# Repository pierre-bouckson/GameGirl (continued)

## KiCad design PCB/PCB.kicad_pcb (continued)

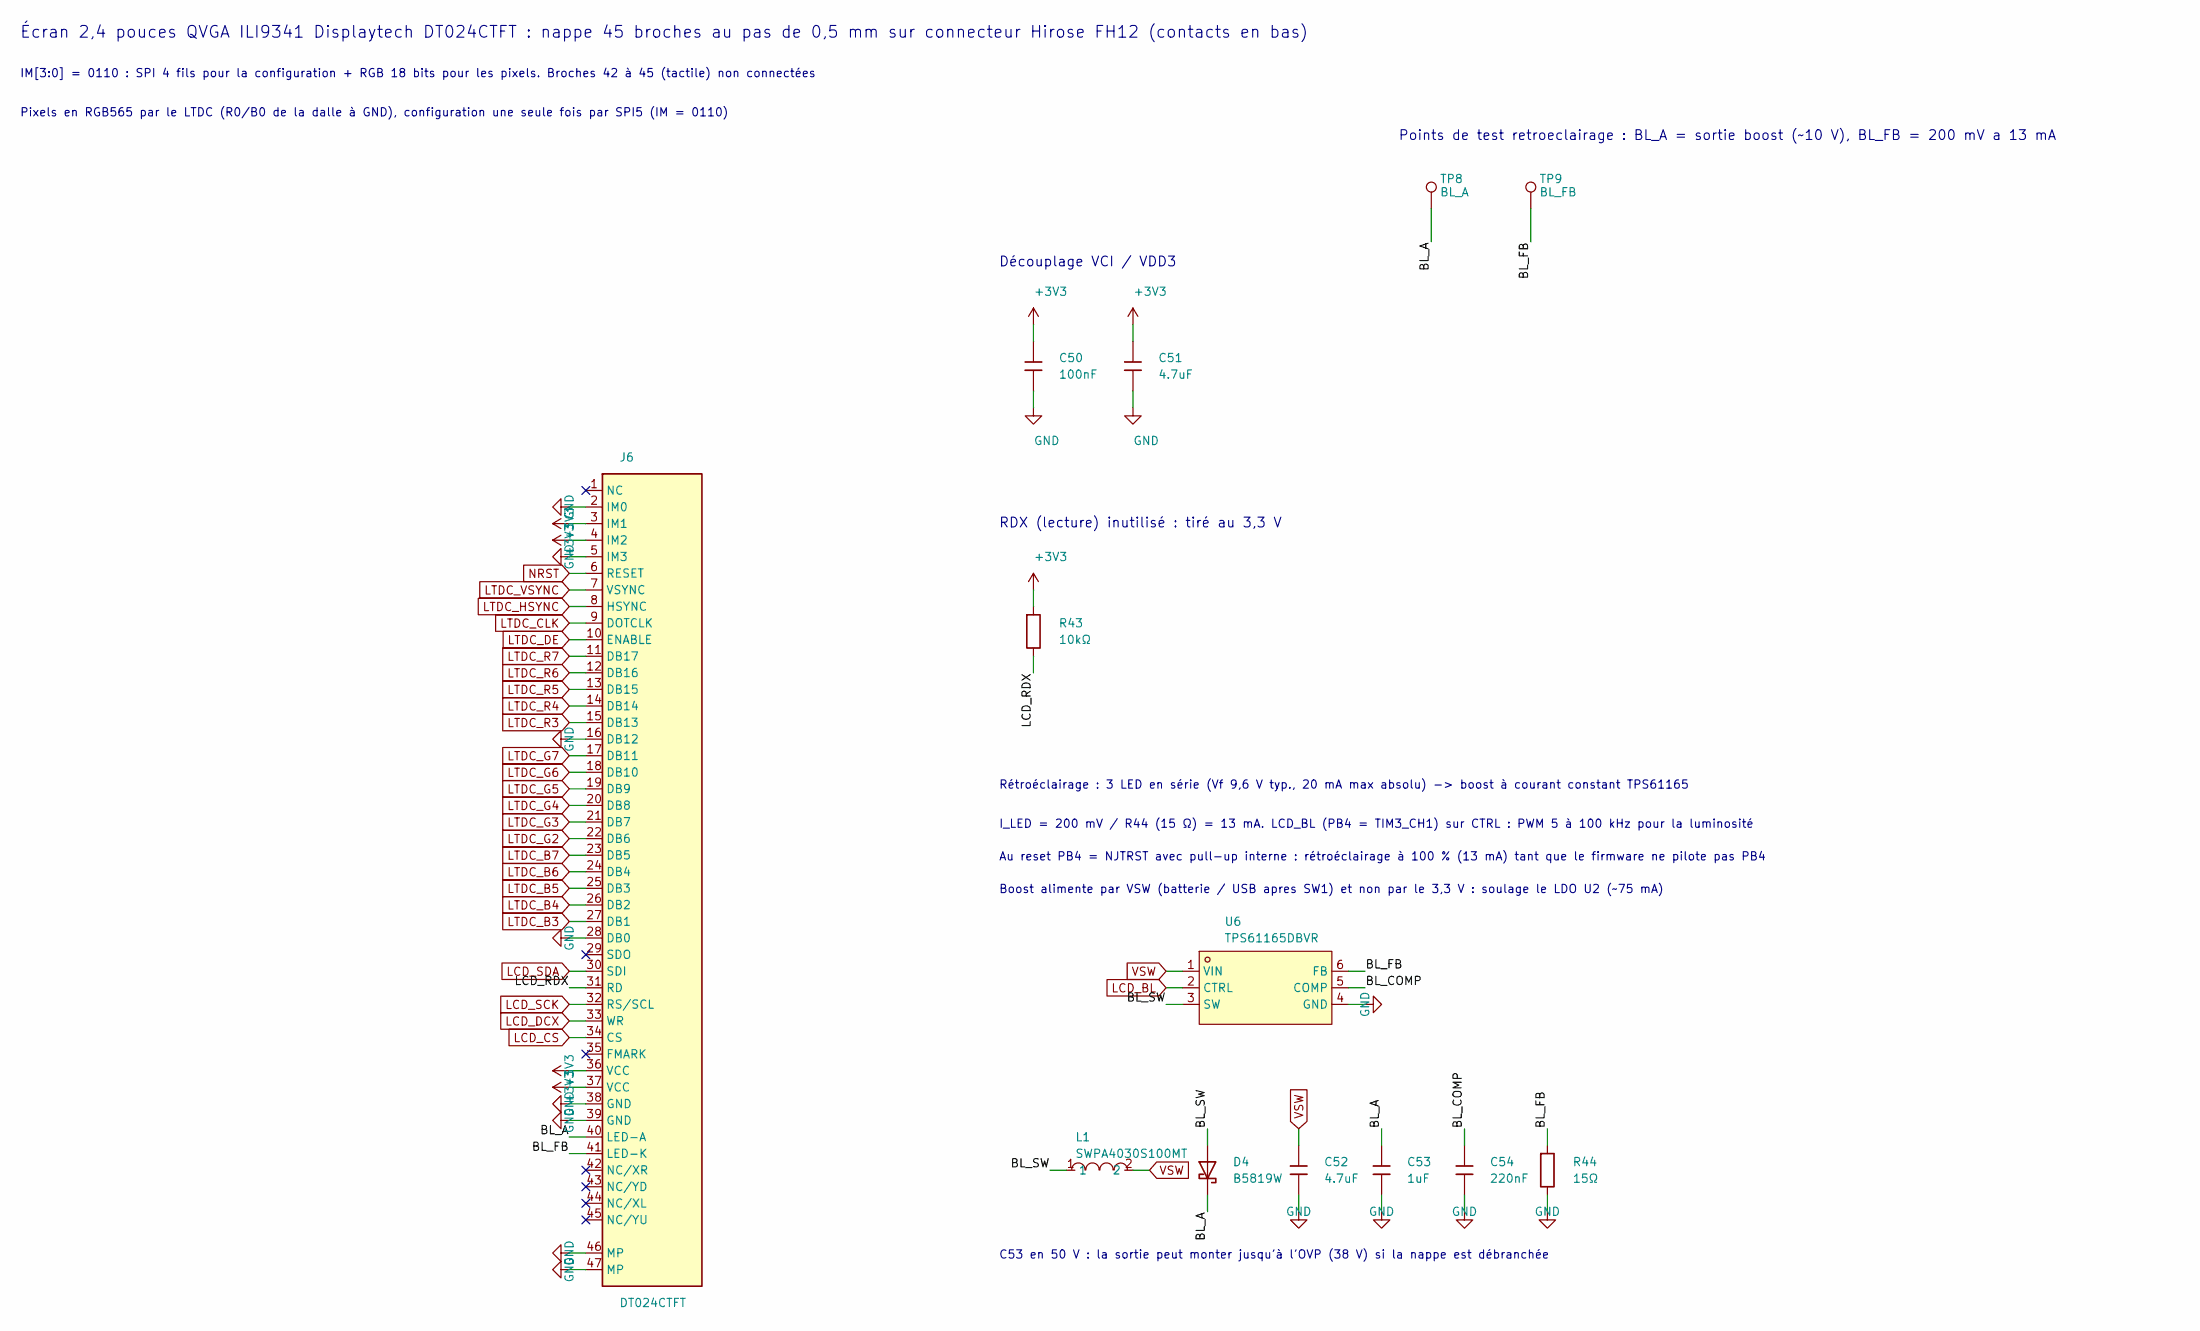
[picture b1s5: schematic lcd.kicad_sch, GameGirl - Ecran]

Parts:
C50: 100nF; C_0402; LCSC C1525
C51: 4.7uF; C_0603; LCSC C19666
C52: 4.7uF; C_0603; Voltage Rated 16V; Tolerance ±10%; Part CL10A475KO8NNNC; LCSC C19666
C53: 1uF; C_0805; Voltage Rated 50V; Tolerance ±10%; Part CL21B105KBFNNNE; LCSC C28323
C54: 220nF; C_0402; Voltage Rated 16V; Tolerance ±10%; Part CL05B224KO5NNNC; LCSC C16772
D4: B5819W; D_SOD-123; Forward Voltage (Vf@If) 900mV@3A; Reverse Voltage (Vr) 40V; Part B5819W; LCSC C64885
J6: DT024CTFT; CONN-SMD_FH12-45S-0.5SH-55; MPN FH12-45S-0.5SH(55); LCSC C3168432
L1: SWPA4030S100MT; IND-SMD_L4.0-W4.0; MPN SWPA4030S100MT; LCSC Part C38117
R43: 10kΩ; R_0402; LCSC C25744
R44: 15Ω; R_0603; LCSC C22810
TP8: BL_A; TestPoint_Pad_D1.5mm
TP9: BL_FB; TestPoint_Pad_D1.5mm
U6: TPS61165DBVR; SOT-23-6_L2.9-W1.6-P0.95-LS2.8-BR; MPN TPS61165DBVR; LCSC Part C58756

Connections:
+3V3: C50.1, C51.1, J6.3 (IM1), J6.4 (IM2), J6.36 (VCC), J6.37 (VCC), R43.1; also elsewhere on the board
/Ecran/BL_A: C53.1, D4.1, J6.40 (LED-A), TP8.1
/Ecran/BL_COMP: C54.1, U6.5 (COMP)
/Ecran/BL_FB: J6.41 (LED-K), R44.1, TP9.1, U6.6 (FB)
/Ecran/BL_SW: D4.2, L1.1, U6.3 (SW)
/Ecran/LCD_RDX: J6.31 (RD), R43.2
GND: C50.2, C51.2, C52.2, C53.2, C54.2, J6.2 (IM0), J6.5 (IM3), J6.16 (DB12), J6.28 (DB0), J6.38 (GND), J6.39 (GND), J6.46 (MP), J6.47 (MP), R44.2, U6.4 (GND); also elsewhere on the board
LCD_BL: U6.2 (CTRL); also elsewhere on the board
LCD_CS: J6.34 (CS); also elsewhere on the board
LCD_DCX: J6.33 (WR); also elsewhere on the board
LCD_SCK: J6.32 (RS/SCL); also elsewhere on the board
LCD_SDA: J6.30 (SDI); also elsewhere on the board
LTDC_B3: J6.27 (DB1); also elsewhere on the board
LTDC_B4: J6.26 (DB2); also elsewhere on the board
LTDC_B5: J6.25 (DB3); also elsewhere on the board
LTDC_B6: J6.24 (DB4); also elsewhere on the board
LTDC_B7: J6.23 (DB5); also elsewhere on the board
LTDC_CLK: J6.9 (DOTCLK); also elsewhere on the board
LTDC_DE: J6.10 (ENABLE); also elsewhere on the board
LTDC_G2: J6.22 (DB6); also elsewhere on the board
LTDC_G3: J6.21 (DB7); also elsewhere on the board
LTDC_G4: J6.20 (DB8); also elsewhere on the board
LTDC_G5: J6.19 (DB9); also elsewhere on the board
LTDC_G6: J6.18 (DB10); also elsewhere on the board
LTDC_G7: J6.17 (DB11); also elsewhere on the board
LTDC_HSYNC: J6.8 (HSYNC); also elsewhere on the board
LTDC_R3: J6.15 (DB13); also elsewhere on the board
LTDC_R4: J6.14 (DB14); also elsewhere on the board
LTDC_R5: J6.13 (DB15); also elsewhere on the board
LTDC_R6: J6.12 (DB16); also elsewhere on the board
LTDC_R7: J6.11 (DB17); also elsewhere on the board
LTDC_VSYNC: J6.7 (VSYNC); also elsewhere on the board
NRST: J6.6 (RESET); also elsewhere on the board
VSW: C52.1, L1.2, U6.1 (VIN); also elsewhere on the board

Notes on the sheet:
Pixels en RGB565 par le LTDC (R0/B0 de la dalle à GND), configuration une seule fois par SPI5 (IM = 0110)
Écran 2,4 pouces QVGA ILI9341 Displaytech DT024CTFT : nappe 45 broches au pas de 0,5 mm sur connecteur Hirose FH12 (contacts en bas)
Découplage VCI / VDD3
I_LED = 200 mV / R44 (15 Ω) = 13 mA. LCD_BL (PB4 = TIM3_CH1) sur CTRL : PWM 5 à 100 kHz pour la luminosité
Au reset PB4 = NJTRST avec pull-up interne : rétroéclairage à 100 % (13 mA) tant que le firmware ne pilote pas PB4
Rétroéclairage : 3 LED en série (Vf 9,6 V typ., 20 mA max absolu) -> boost à courant constant TPS61165
C53 en 50 V : la sortie peut monter jusqu'à l'OVP (38 V) si la nappe est débranchée
Points de test retroeclairage : BL_A = sortie boost (~10 V), BL_FB = 200 mV a 13 mA
IM[3:0] = 0110 : SPI 4 fils pour la configuration + RGB 18 bits pour les pixels. Broches 42 à 45 (tactile) non connectées
Boost alimente par VSW (batterie / USB apres SW1) et non par le 3,3 V : soulage le LDO U2 (~75 mA)
RDX (lecture) inutilisé : tiré au 3,3 V

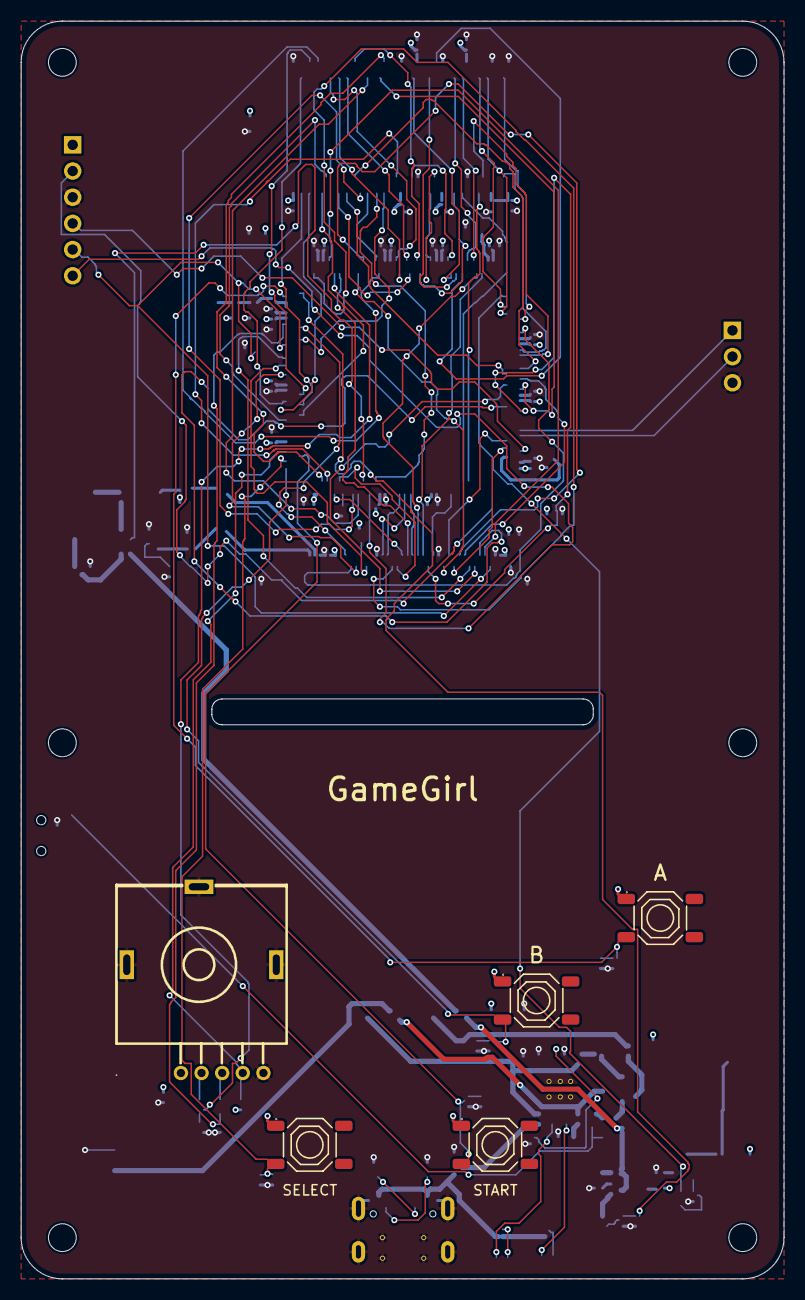
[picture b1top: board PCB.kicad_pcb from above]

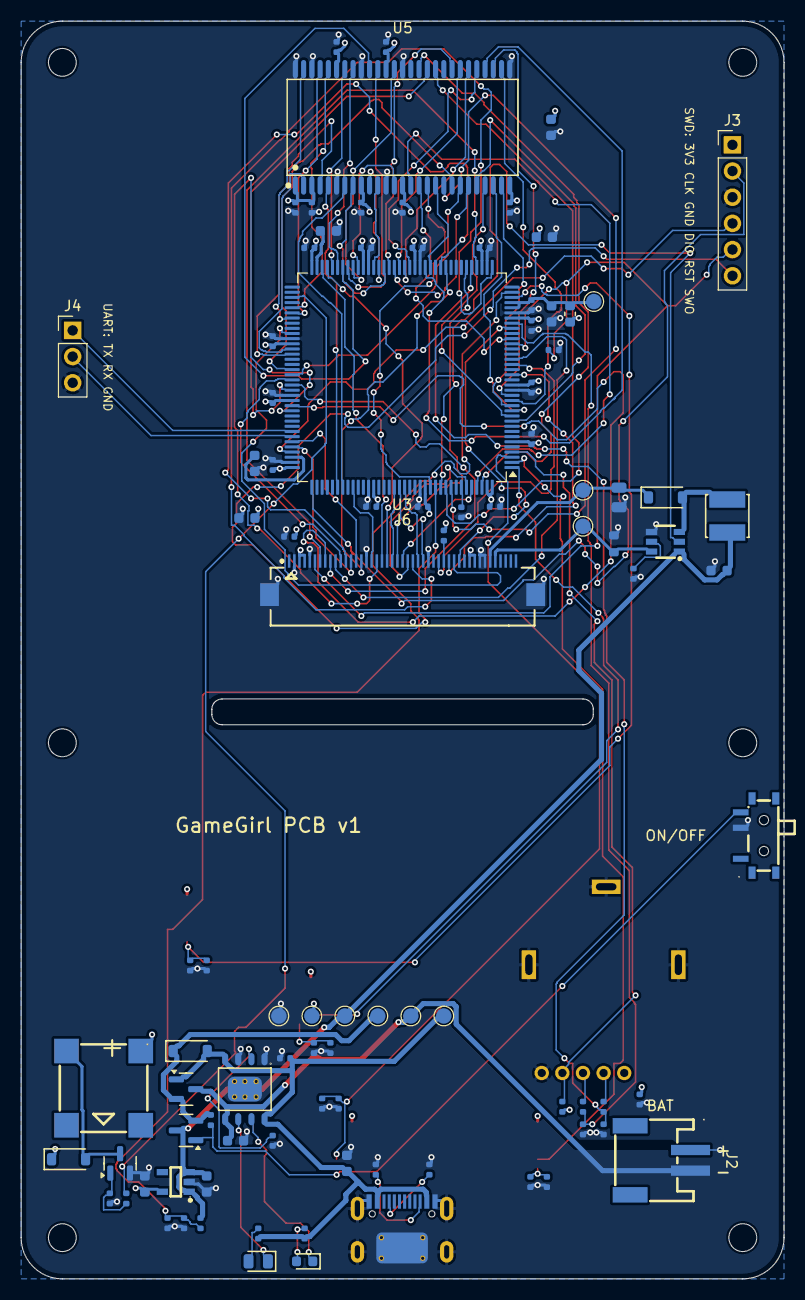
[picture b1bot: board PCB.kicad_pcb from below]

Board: 4 copper layers, 74.0 x 122.0 mm, 107 parts (96 on the bottom side), 105 nets.

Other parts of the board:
H1, H2, H3, H4, H5, H6: M2.5; MountingHole_2.7mm_M2.5

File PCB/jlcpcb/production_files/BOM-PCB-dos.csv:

Comment,Designator,Footprint,LCSC,Quantity
1.5kΩ,R3,R_0402,C25867,1
100kΩ,"R7,R8,R10,R38",R_0402,C25741,4
100nF,"C5,C6,C7,C8,C9,C10,C11,C12,C13,C14,C15,C16,C17,C20,C23,C24,C30,C31,C32,C33,C34,C35,C36,C40,C41,C42,C43,C44,C45,C46,C50",C_0402,C1525,31
100Ω,R37,R_0402,C25076,1
10kΩ,"R6,R9,R22,R23,R24,R25,R26,R43",R_0402,C25744,8
10uF,"C1,C2,C3,C4,C47",C_0603,C19702,5
15Ω,R44,R_0603,C22810,1
1N4148W,D5,D_SOD-123,C81598,1
1kΩ,"R4,R5,R20,R21",R_0402,C11702,4
1uF,C19,C_0603,C15849,1
1uF,C53,C_0805,C28323,1
2.2uF,"C21,C22",C_0603,C23630,2
220nF,C54,C_0402,C16772,1
4.7uF,"C18,C51,C52",C_0603,C19666,3
5.1kΩ,"R1,R2",R_0402,C25905,2
600Ω@100MHz,FB1,FB_0603,C1002,1
AO3400A,Q2,Q_SOT-23,C20917,1
AO3401A,"Q1,Q3",Q_SOT-23,C15127,2
AP2112K-3.3TRG1,U2,SOT-25-5_L2.9-W1.6-P0.95-LS2.8-BL,C51118,1
B5819W,"D1,D4",D_SOD-123,C64885,2
BATT JST-PH 2 mm,J2,CONN-SMD_P2.00_S2B-PH-SM4-TB-LF-SN,C295747,1
DT024CTFT,J6,CONN-SMD_FH12-45S-0.5SH-55,C3168432,1
IS42S16400J-7TLI,U5,TSOP-54_L22.2-W10.2-P0.80-LS11.8-BL,C2979137,1
MLT-8530,BZ1,BUZ-SMD_4P-L8.5-W8.5-P8.50-BR,C94599,1
ON/OFF,SW1,SW-TH_MSK12C02,C431540,1
Rouge : en charge,D2,D_0603,C2286,1
STM32F429ZIT6,U3,LQFP-144_20x20mm_P0.5mm,C84808,1
SWPA4030S100MT,L1,IND-SMD_L4.0-W4.0,C38117,1
TP4056,U1,ESOP-8_L4.9-W3.9-P1.27-LS6.0-BL-EP,C16581,1
TPS61165DBVR,U6,SOT-23-6_L2.9-W1.6-P0.95-LS2.8-BR,C58756,1
USB-C 16P,J1,TYPE-C-SMD_HX-TYPE-C-16PIN,C2927039,1
Vert : chargée,D3,D_0805,C2297,1

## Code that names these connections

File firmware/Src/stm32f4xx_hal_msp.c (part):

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    __HAL_RCC_GPIOC_CLK_ENABLE();
    __HAL_RCC_GPIOA_CLK_ENABLE();
    /**ADC1 GPIO Configuration
    PC3     ------> ADC1_IN13
    PA1     ------> ADC1_IN1
    PA5     ------> ADC1_IN5
    */
    GPIO_InitStruct.Pin = GPIO_PIN_3;
    GPIO_InitStruct.Mode = GPIO_MODE_ANALOG;
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    __HAL_RCC_ADC1_CLK_DISABLE();

    /**ADC1 GPIO Configuration
    PC3     ------> ADC1_IN13
    PA1     ------> ADC1_IN1
    PA5     ------> ADC1_IN5
    */
    HAL_GPIO_DeInit(GPIOC, GPIO_PIN_3);

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    __HAL_RCC_GPIOC_CLK_ENABLE();
    __HAL_RCC_GPIOD_CLK_ENABLE();
    /**LTDC GPIO Configuration
    PF10     ------> LTDC_DE
    PA3     ------> LTDC_B5
    PA4     ------> LTDC_VSYNC
    PA6     ------> LTDC_G2
    PB0     ------> LTDC_R3
    PB1     ------> LTDC_R6
    PB10     ------> LTDC_G4
    PB11     ------> LTDC_G5
    PG6     ------> LTDC_R7
    PG7     ------> LTDC_CLK
    PC6     ------> LTDC_HSYNC
    PC7     ------> LTDC_G6
    PA11     ------> LTDC_R4
    PA12     ------> LTDC_R5
    PD3     ------> LTDC_G7
    PG10     ------> LTDC_G3
    PG11     ------> LTDC_B3
    PG12     ------> LTDC_B4
    PB8     ------> LTDC_B6
    PB9     ------> LTDC_B7
    */
    GPIO_InitStruct.Pin = GPIO_PIN_10;
    GPIO_InitStruct.Mode = GPIO_MODE_AF_PP;
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    __HAL_RCC_LTDC_CLK_DISABLE();

    /**LTDC GPIO Configuration
    PF10     ------> LTDC_DE
    PA3     ------> LTDC_B5
    PA4     ------> LTDC_VSYNC
    PA6     ------> LTDC_G2
    PB0     ------> LTDC_R3
    PB1     ------> LTDC_R6
    PB10     ------> LTDC_G4
    PB11     ------> LTDC_G5
    PG6     ------> LTDC_R7
    PG7     ------> LTDC_CLK
    PC6     ------> LTDC_HSYNC
    PC7     ------> LTDC_G6
    PA11     ------> LTDC_R4
    PA12     ------> LTDC_R5
    PD3     ------> LTDC_G7
    PG10     ------> LTDC_G3
    PG11     ------> LTDC_B3
    PG12     ------> LTDC_B4
    PB8     ------> LTDC_B6
    PB9     ------> LTDC_B7
    */
    HAL_GPIO_DeInit(GPIOF, GPIO_PIN_10);

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
    __HAL_RCC_GPIOF_CLK_ENABLE();
    /**SPI5 GPIO Configuration
    PF7     ------> SPI5_SCK
    PF9     ------> SPI5_MOSI
    */
    GPIO_InitStruct.Pin = GPIO_PIN_7|GPIO_PIN_9;
    GPIO_InitStruct.Mode = GPIO_MODE_AF_PP;
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    __HAL_RCC_SPI5_CLK_DISABLE();

    /**SPI5 GPIO Configuration
    PF7     ------> SPI5_SCK
    PF9     ------> SPI5_MOSI
    */
    HAL_GPIO_DeInit(GPIOF, GPIO_PIN_7|GPIO_PIN_9);

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
    __HAL_RCC_GPIOB_CLK_ENABLE();
    /**TIM3 GPIO Configuration
    PB4     ------> TIM3_CH1
    */
    GPIO_InitStruct.Pin = GPIO_PIN_4;
    GPIO_InitStruct.Mode = GPIO_MODE_AF_PP;
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
    __HAL_RCC_GPIOA_CLK_ENABLE();
    /**USART1 GPIO Configuration
    PA9     ------> USART1_TX
    PA10     ------> USART1_RX
    */
    GPIO_InitStruct.Pin = GPIO_PIN_9|GPIO_PIN_10;
    GPIO_InitStruct.Mode = GPIO_MODE_AF_PP;
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    __HAL_RCC_USART1_CLK_DISABLE();

    /**USART1 GPIO Configuration
    PA9     ------> USART1_TX
    PA10     ------> USART1_RX
    */
    HAL_GPIO_DeInit(GPIOA, GPIO_PIN_9|GPIO_PIN_10);

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  __HAL_RCC_FMC_CLK_ENABLE();

  /** FMC GPIO Configuration
  PF0   ------> FMC_A0
  PF1   ------> FMC_A1
  PF2   ------> FMC_A2
  PF3   ------> FMC_A3
  PF4   ------> FMC_A4
  PF5   ------> FMC_A5
  PC0   ------> FMC_SDNWE
  PF11   ------> FMC_SDNRAS
  PF12   ------> FMC_A6
  PF13   ------> FMC_A7
  PF14   ------> FMC_A8
  PF15   ------> FMC_A9
  PG0   ------> FMC_A10
  PG1   ------> FMC_A11
  PE7   ------> FMC_D4
  PE8   ------> FMC_D5
  PE9   ------> FMC_D6
  PE10   ------> FMC_D7
  PE11   ------> FMC_D8
  PE12   ------> FMC_D9
  PE13   ------> FMC_D10
  PE14   ------> FMC_D11
  PE15   ------> FMC_D12
  PD8   ------> FMC_D13
  PD9   ------> FMC_D14
  PD10   ------> FMC_D15
  PD14   ------> FMC_D0
  PD15   ------> FMC_D1
  PG4   ------> FMC_BA0
  PG5   ------> FMC_BA1
  PG8   ------> FMC_SDCLK
  PD0   ------> FMC_D2
  PD1   ------> FMC_D3
  PG15   ------> FMC_SDNCAS
  PB5   ------> FMC_SDCKE1
  PB6   ------> FMC_SDNE1
  PE0   ------> FMC_NBL0
  PE1   ------> FMC_NBL1
  */
  GPIO_InitStruct.Pin = GPIO_PIN_0|GPIO_PIN_1|GPIO_PIN_2|GPIO_PIN_3
                          |GPIO_PIN_4|GPIO_PIN_5|GPIO_PIN_11|GPIO_PIN_12
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  __HAL_RCC_FMC_CLK_DISABLE();

  /** FMC GPIO Configuration
  PF0   ------> FMC_A0
  PF1   ------> FMC_A1
  PF2   ------> FMC_A2
  PF3   ------> FMC_A3
  PF4   ------> FMC_A4
  PF5   ------> FMC_A5
  PC0   ------> FMC_SDNWE
  PF11   ------> FMC_SDNRAS
  PF12   ------> FMC_A6
  PF13   ------> FMC_A7
  PF14   ------> FMC_A8
  PF15   ------> FMC_A9
  PG0   ------> FMC_A10
  PG1   ------> FMC_A11
  PE7   ------> FMC_D4
  PE8   ------> FMC_D5
  PE9   ------> FMC_D6
  PE10   ------> FMC_D7
  PE11   ------> FMC_D8
  PE12   ------> FMC_D9
  PE13   ------> FMC_D10
  PE14   ------> FMC_D11
  PE15   ------> FMC_D12
  PD8   ------> FMC_D13
  PD9   ------> FMC_D14
  PD10   ------> FMC_D15
  PD14   ------> FMC_D0
  PD15   ------> FMC_D1
  PG4   ------> FMC_BA0
  PG5   ------> FMC_BA1
  PG8   ------> FMC_SDCLK
  PD0   ------> FMC_D2
  PD1   ------> FMC_D3
  PG15   ------> FMC_SDNCAS
  PB5   ------> FMC_SDCKE1
  PB6   ------> FMC_SDNE1
  PE0   ------> FMC_NBL0
  PE1   ------> FMC_NBL1
  */
  HAL_GPIO_DeInit(GPIOF, GPIO_PIN_0|GPIO_PIN_1|GPIO_PIN_2|GPIO_PIN_3
                          |GPIO_PIN_4|GPIO_PIN_5|GPIO_PIN_11|GPIO_PIN_12
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
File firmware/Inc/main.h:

/* USER CODE BEGIN Header */
/**
  ******************************************************************************
  * @file           : main.h
  * @brief          : Header for main.c file.
  *                   This file contains the common defines of the application.
  ******************************************************************************
  * @attention
  *
  * Copyright (c) 2026 STMicroelectronics.
  * All rights reserved.
  *
  * This software is licensed under terms that can be found in the LICENSE file
  * in the root directory of this software component.
  * If no LICENSE file comes with this software, it is provided AS-IS.
  *
  ******************************************************************************
  */
/* USER CODE END Header */

/* Define to prevent recursive inclusion -------------------------------------*/
#ifndef __MAIN_H
#define __MAIN_H

#ifdef __cplusplus
extern "C" {
#endif

/* Includes ------------------------------------------------------------------*/
#include "stm32f4xx_hal.h"

/* Private includes ----------------------------------------------------------*/
/* USER CODE BEGIN Includes */

#include "ili9341.h"
#include "stm32f429i_discovery.h"

/* USER CODE END Includes */

/* Exported types ------------------------------------------------------------*/
/* USER CODE BEGIN ET */

/* USER CODE END ET */

/* Exported constants --------------------------------------------------------*/
/* USER CODE BEGIN EC */

/* Séquence de l'ADC1 (scan continu + DMA circulaire), dans l'ordre des rangs.
 * Sur la GameGirl, le joystick est monté tourné : PA5 (rang 0) donne l'axe Y
 * du jeu et PC3 (rang 1) l'axe X, d'où les deux index croisés. */
#define ADC_IDX_JOY_Y    0   /* canal 5, PA5 */
#define ADC_IDX_JOY_X    1   /* canal 13, PC3 */
#define ADC_IDX_VBAT     2   /* canal 1, PA1 = VBAT_SENSE (VSW / 2) */
#define ADC_IDX_VREFINT  3   /* référence interne 1,21 V, pour connaître VDDA */
#define ADC_NB_CHANNELS  4

/* USER CODE END EC */

/* Exported macro ------------------------------------------------------------*/
/* USER CODE BEGIN EM */

/* USER CODE END EM */

/* Exported functions prototypes ---------------------------------------------*/
void HAL_TIM_MspPostInit(TIM_HandleTypeDef *htim);
void Error_Handler(void);

/* USER CODE BEGIN EFP */

/* Valeurs ADC brutes (12 bits), remplies en continu par DMA ; index ADC_IDX_* */
extern volatile uint16_t adc_values[ADC_NB_CHANNELS];

/* USER CODE END EFP */

/* Private defines -----------------------------------------------------------*/

/* USER CODE BEGIN Private defines */

/* USER CODE END Private defines */

#ifdef __cplusplus
}
#endif

#endif /* __MAIN_H */
